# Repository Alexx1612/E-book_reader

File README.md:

## OPENBOOK E-BOOK READER
OpenBook – Proiect TSC 2025
OpenBook este un prototip de eBook reader open-source, dezvoltat în jurul microcontrolerului ESP32-C6. Dispozitivul este echipat cu un afișaj E-Ink, baterie Li-Po, încărcare prin USB-C, slot pentru card microSD și o serie de senzori de mediu. Proiectul a presupus realizarea completă a schemei electrice, proiectarea plăcii PCB, modelarea 3D și generarea fișierelor pentru fabricație.

## Diagrama bloc

### Caracteristici Cheie
- **Alimentare prin USB-C**  
  Permite programarea ușoară și încărcarea bateriei, asigurând o integrare simplificată cu sursa de alimentare.
- **Microcontroller ESP32-C6**  
  Dispune de un nucleu RISC-V, Wi-Fi 6, BLE și 8MB memorie flash internă pentru aplicații complexe și conectivitate modernă.
- **Senzori Integrați**  
  - **BME688:** Măsoară temperatura, umiditatea, presiunea și concentrațiile de gaze.  
  - **DS3231:** Modul RTC de înaltă precizie, care menține ceasul de timp real chiar și în absența alimentării principale.
- **Stocare Suplimentară**  
  - **Card SD (SPI):** Permite stocarea locală a e-book-urilor și datelor adiționale.  
  - **Memorie NOR Flash (W25Q512):** Oferă spațiu suplimentar de stocare prin interfața SPI.
- **Afișaj E-Paper**  
  Realizează afișajul e-book-urilor cu consum ultra-redus, prin actualizări doar la nevoie.
- **Monitorizare Baterie**  
  Modulul MAX17048 monitorizează nivelul de încărcare al bateriei, contribuind la gestionarea eficientă a consumului de energie.

## Bill of materials (BOM)

| Component                          | Supplier Link                                                                                                                                                 | Datasheet                                                                                                         |
|------------------------------------|---------------------------------------------------------------------------------------------------------------------------------------------------------------|-------------------------------------------------------------------------------------------------------------------|
| XC6220A331MR-G                     | [Model](https://componentsearchengine.com/part-view/XC6220A331MR-G/Torex)                                                                                      | [Datasheet](https://product.torexsemi.com/system/files/series/xc6220.pdf)                                            |
| W25Q512JVEIQ                       | [Model](https://www.snapeda.com/parts/W25Q512JVEIQ/Winbond+Electronics/view-part/?ref=eda)                                                                        | [Datasheet](https://www.winbond.com/resource-files/W25Q512JV%20SPI%20RevB%2006252019%20KMS.pdf)                      |
| USBLC6-2SC6Y                       | [Model](https://www.snapeda.com/parts/USBLC6-2SC6Y/STMicroelectronics/view-part/?welcome=home&ref=eda)                                                            | [Datasheet](https://www.snapeda.com/parts/USBLC6-2SC6Y/STMicroelectronics/datasheet/)                              |
| USB4110-GF-A                       | [Model](https://componentsearchengine.com/part-view/USB4110-GF-A/GCT%20(GLOBAL%20CONNECTOR%20TECHNOLOGY))                                                        | [Datasheet](https://gct.co/files/drawings/usb4110.pdf)                                                             |
| SJ                                 | [Model](https://grabcad.com/library/solder-jumpers-1)                                                                                                          | [Datasheet]()                                                                                                     |
| SI1308EDL-T1-GE3 MOSFET             | [Model](https://www.snapeda.com/parts/SI1308EDL-T1-GE3/Vishay+Siliconix/view-part/?welcome=home&ref=eda)                                                        | [Datasheet](https://www.snapeda.com/parts/SI1308EDL-T1-GE3/Vishay%20Siliconix/datasheet/)                           |
| Resistor 0402                      | [Model](https://grabcad.com/library/resistor-0402-1)                                                                                                           | [Datasheet](https://www.yageo.com/upload/media/product/products/datasheet/rchip/PYu-RC_Group_51_RoHS_L_12.pdf)       |
| RCL CPOL 3528                      | [Model](https://www.snapeda.com/parts/CPH3225A/Seiko+Instruments/view-part/?ref=eda)                                                                             | [Datasheet](https://s3.amazonaws.com/snapeda/datasheet/TAJB475K025RNJ_AVX.pdf)                                     |
| QWIIC Connector                    | [Model](https://www.snapeda.com/parts/PRT-14417/SparkFun/view-part/)                                                                                           | [Datasheet](https://www.snapeda.com/parts/PRT-14417/SparkFun%20Electronics/datasheet/)                              |
| PGB1010603MR                       | [Model](https://www.snapeda.com/parts/PGB1010603MR/Littelfuse/view-part/?ref=eda)                                                                               | [Datasheet](https://www.snapeda.com/parts/PGB1010603MR/Littelfuse%20Inc./datasheet/)                                |
| MBR0530 Schottky Diode             | [Model](https://www.snapeda.com/parts/MBR0530/Onsemi/view-part/?ref=snap)                                                                                        | [Datasheet](https://www.snapeda.com/parts/MBR0530/ON%20Semiconductor/datasheet/)                                   |
| MAX17048G+T10                      | [Model](https://www.snapeda.com/parts/MAX17048G+T10/Analog+Devices/view-part/?ref=eda)                                                                            | [Datasheet](https://www.snapeda.com/parts/MAX17048G+T10/Analog%20Devices/datasheet/)                                |
| LED Chip 0603                      | [Model](https://www.snapeda.com/parts/KP-1608SURCK/Kingbright/view-part/?ref=search&t=LED%200603)                                                                 | [Datasheet](https://www.snapeda.com/parts/KP-1608SURCK/Kingbright/datasheet/)                                      |
| FH34SRJ-24S-0.5SH                  | [Model](https://ro.mouser.com/ProductDetail/Hirose-Connector/FH34SRJ-24S-0.5SH99?qs=vcbW%252B4%252BSTIpKBl5ap9J8Fw%3D%3D)                                       | [Datasheet](https://www.snapeda.com/parts/FH34SRJ-24S-0.5SH(99)/Hirose%20Connector/datasheet/)                     |
| ESP32C6 WROOM-1-N8                 | [Model](https://www.snapeda.com/parts/ESP32-C6-WROOM-1-N8/Espressif+Systems/view-part/?ref=eda)                                                                    | [Datasheet](https://www.snapeda.com/parts/ESP32-C6-WROOM-1-N8/Espressif%20Systems/datasheet/)                       |
| ESP32C6 Varistor 1812              | [Model]()                                                                                                                                                      | [Datasheet]()                                                                                                     |
| ESP32 WROVER MCP73831 Power Management | [Model](https://www.snapeda.com/parts/BME680/Bosch/view-part/?welcome=home)                                                                                 | [Datasheet](https://www.snapeda.com/parts/MCP73831T-2ACI/OT/Microchip/datasheet/)                                  |
| ESP32 WROVER BME680 Sensor         | [Model](https://www.snapeda.com/parts/BME680/Bosch/view-part/?welcome=home)                                                                                     | [Datasheet](https://www.bosch-sensortec.com/media/boschsensortec/downloads/datasheets/bst-bme680-ds001.pdf)         |
| ESP32 WROVER 0805 Capacitor        | [Model]()                                                                                                                                                      | [Datasheet]()                                                                                                     |
| DS3231SN                           | [Model](https://www.snapeda.com/parts/DS3231SN%23/Analog+Devices/view-part/?ref=eda)                                                                             | [Datasheet](https://www.snapeda.com/parts/DS3231SN%23/Analog%20Devices/datasheet/)                                  |
| Custom Button                      | [Model](https://industry.panasonic.com/global/en/products/control/switch/light-touch/number/evqpuj02k)                                                            | [Datasheet](https://industry.panasonic.com/global/en/downloads?tab=catalog&small_g_cd=203&part_no=EVQPUJ02K)         |
| CPH3225A                         | [Model](https://www.snapeda.com/parts/CPH3225A/Seiko+Instruments/view-part/?ref=snap)                                                                           | [Datasheet](https://www.snapeda.com/parts/CPH3225A/Seiko%20Instruments/datasheet/)                                |
| Capacitor 0402                     | [Model](https://ro.mouser.com/c/passive-components/capacitors/ceramic-capacitors/?q=CC0402&srsltid=AfmBOoogjqwwed3xvp6V5-bfVkRuawirfMcnAC47L-UQdC3mnXJk097M) | [Datasheet](https://componentsearchengine.com/Datasheets/2/CC0402MRX5R5BB106.pdf)                                  |
| BD5229G-TR                         | [Model](https://componentsearchengine.com/part-view/BD5229G-TR/ROHM%20Semiconductor)                                                                            | [Datasheet](https://fscdn.rohm.com/en/products/databook/datasheet/ic/power/voltage_detector/bd52xxg-e.pdf)         |
| 744043680                          | [Model](https://ro.mouser.com/ProductDetail/Wurth-Elektronik/744043680?qs=PGXP4M47uW6VkZq%252BkzjrHA%3D%3D)                                                   | [Datasheet](https://www.we-online.com/components/products/datasheet/744043680.pdf)                                  |
| 112A-TAAR-R03                      | [Model](https://store.comet.srl.ro/Catalogue/Product/43497/)                                                                                                  | [Datasheet](https://www.snapeda.com/parts/112A-TAAR-R03/Attend/datasheet/)                                         |

## Consum

| Component                        | Current Draw (mA) | Voltage (V) | Power (mW)   |
|----------------------------------|-------------------|-------------|--------------|
| ESP32-C6 (Wi-Fi active)          | 200               | 3.3         | 660          |
| E-Paper Display (Updating)       | 40                | 3.3         | 132          |
| BME688 Sensor (Measuring)        | 3.1               | 3.3         | 10.23        |
| RTC Module (Active)              | 0.15              | 3.3         | 0.495        |
| SD Card (Active)                 | 50                | 3.3         | 165          |
| Externar NOR Flash               | 25                | 3.3         | 82.5         |
| **Total Estimated Power Consumption** | ~318.5 mA         | 3.3         | 1050.72      |

### Arhitectura Hardware
- **Alimentare și Protecție:**  
  Sistemul beneficiază de alimentare prin USB-C și include protecții ESD (varistori, diodă TVS) pentru siguranța componentelor. Circuitul de încărcare Li-Po (MCP73831) și regulatorul LDO asigură o tensiune stabilă de 3.3V.
- **Conectivitate și Interfețe:**  
  Microcontrollerul ESP32-C6-WROOM-1 acționează ca nucleu central, conectând diferite periferice prin:
  - **SPI:** Utilizat pentru afișajul E-Paper, Cardul SD și memoria NOR Flash.  
  - **I2C:** Folosit pentru senzorii BME688 și DS3231, precum și pentru monitorizarea bateriei.  
  - **GPIO:** Gestionarea butoanelor de control (RESET, BOOT) și alte funcții digitale.

### Mapare Pini ESP32-C6
| Component                                | ESP32-C6 Pin(s)                                                     | Interface | Scop                                                                                   |
|------------------------------------------|---------------------------------------------------------------------|-----------|----------------------------------------------------------------------------------------|
| **E-Paper Display**                      | IO7 (MOSI), IO6 (SCK), IO10 (CS), IO5 (DC), IO23 (RST), IO3 (BUSY)    | SPI       | Transferă datele imaginii către afișaj și controlează starea acestuia.                  |
| **Battery Monitoring (MAX17048)**        | IO21 (SDA), IO22 (SCL)                                               | I2C       | Monitorizează tensiunea bateriei și starea de încărcare pentru un management energetic eficient. |
| **USB-C Connection**                     | GPIOs prin circuit de protecție și reglementare                       | USB       | Furnizează alimentarea și permite programarea ESP32-C6.   
| **MicroSD Card**                         | IO7 (MOSI), IO6 (SCK), IO4 (SS_SD), IO2 (MISO)                        | SPI       | Permite stocarea și accesarea fișierelor de e-book.                                     |
| **Environmental Sensor (BME688)**        | IO21 (SDA), IO22 (SCL)                                               | I2C       | Măsoară temperatura, umiditatea, presiunea și calitatea aerului.                        |
| **RTC Module (DS3231)**                  | IO21 (SDA), IO22 (SCL), IO18 (RST), IO1 (32KHz), IO0 (INT_RTC)         | I2C       | Menține ceasul de timp real în mod precis, chiar și în absența alimentării principale.    |
| **External NOR Flash**                   | IO11 (CS), IO6 (SCK), IO2 (MISO), IO7 (MOSI)                          | SPI       | Oferă stocare suplimentară pentru datele aplicațiilor și firmware.                      |
| **Control Buttons**                      | IO9 (BOOT), IO15 (CHANGE), EN (RESET)                                  | GPIO      | Permite interacțiunea utilizatorului prin funcții de boot, reset și alte comenzi digitale.|        

## Observații Suplimentare

- Traseele de alimentare au o lățime de 0.3 mm, iar traseele de semnal sunt proiectate cu o lățime de 0.15 mm, pentru a asigura o transmisie clară și o pierdere minimă de semnal.
- PCB-ul are o grosime de 1 mm și include planuri de masă pe ambele straturi, pentru a optimiza împământarea și a reduce interferențele electromagnetice.
- Conectorii, afișajul E-Paper și bateria au fost integrate în modelul 3D, iar acestea au fost testate riguros pentru a asigura o potrivire perfectă în carcasă.
- Carcasa a fost importată și aliniată cu placa pentru a obține render-uri vizuale realiste, facilitând astfel evaluarea designului final.
- Toate fișierele de proiect au fost verificate prin ERC (Electrical Rules Check) și DRC (Design Rules Check) pentru a asigura conformitatea cu standardele de proiectare și a elimina eventualele erori de fabricație.

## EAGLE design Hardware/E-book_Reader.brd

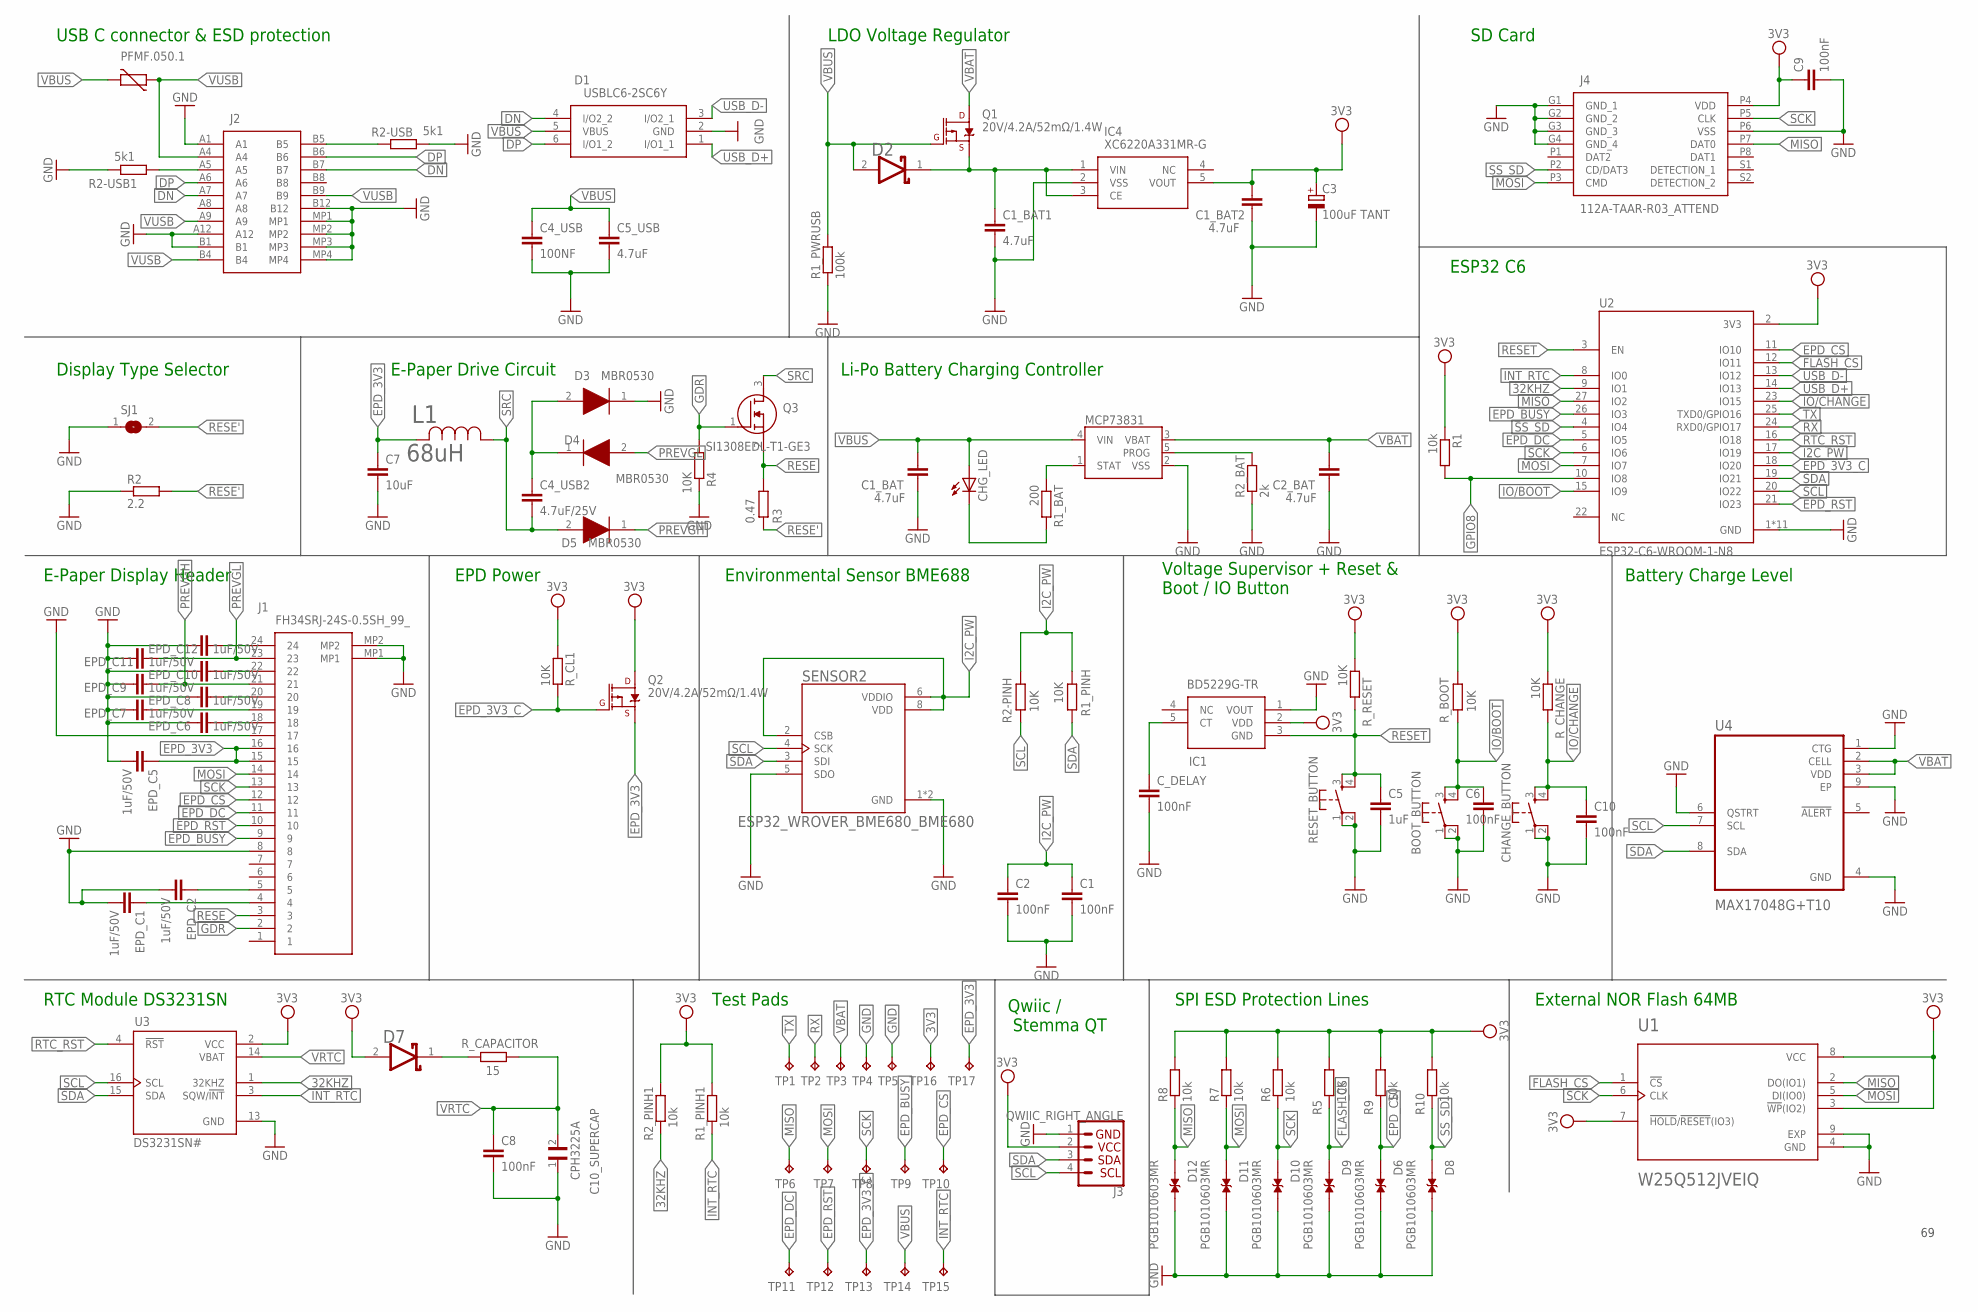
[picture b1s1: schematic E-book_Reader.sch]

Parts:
BOOT_BUTTON: BUTTON_CUSYOMV1; MYBUTTON
C1, C2, C6, C8, C9, C10: 100nF; EAGLE-LTSPICE_C0402
C1_BAT, C1_BAT1, C1_BAT2, C2_BAT, C5_USB: 4.7uF; EAGLE-LTSPICE_C0402
C3: 100uF TANT; RCL_CT3528
C4_USB: 100NF; EAGLE-LTSPICE_C0402
C4_USB2: 4.7uF/25V; EAGLE-LTSPICE_C0402
C5: 1uF; EAGLE-LTSPICE_C0402
C7: 10uF; EAGLE-LTSPICE_C0402
C10_SUPERCAP: CPH3225A; CAPCP3225X100N
CHANGE_BUTTON: BUTTON_CUSYOMV1; MYBUTTON
CHG_LED: ADAFRUIT_LEDCHIP-LED0603; ADAFRUIT_CHIP-LED0603
C_DELAY: 100nF; EAGLE-LTSPICE_C0402
D1: USBLC6-2SC6Y; SOT95P280X145-6N
D2, D7: ESP32_WROVER_AVX---SD0805S020S1R0_AVX_SD0805S020S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; ESP32_WROVER_AVX---SD0805S020S1R0_AVX_SD0805S020S1R0_0
D3, D4, D5: MBR0530; SOD3716X135N
D6, D8, D9, D10, D11, D12: PGB1010603MR; DIOC1608X36N
EPD_C1, EPD_C2, EPD_C5, EPD_C6, EPD_C7, EPD_C8, EPD_C9, EPD_C10, EPD_C11, EPD_C12: 1uF/50V; EAGLE-LTSPICE_C0402
IC1: BD5229G-TR; SOT95P280X125-5N
IC4: XC6220A331MR-G; SOT95P280X120-5N
J1: FH34SRJ-24S-0.5SH_99_; FH34SRJ24S05SH99
J2: SAMACSYS_PARTS_USB4110-GF-A; SAMACSYS_PARTS_USB4110GFA
J3: QWIIC_RIGHT_ANGLE; JST04_1MM_RA
J4: 112A-TAAR-R03_ATTEND; 112ATAARR03ATTEND
L1: 68uH; IND_4828-WE-TPC_WRE
MCP73831: ESP32_WROVER_SPARKFUN-IC-POWER_MCP73831; ESP32_WROVER_SPARKFUN-IC-POWER_SOT23-5
PFMF.050.1: ESP32C6_VARISTORCN1812; ESP32C6_VARISTOR_CT/CN1812
Q1, Q2: 20V/4.2A/52mΩ/1.4W; ESP32_WROVER_SPARKFUN-DISCRETESEMI_SOT23-3
Q3: SI1308EDL-T1-GE3; SOT65P210X110-3N
R1, R1_PINH1, R2_PINH1, R5, R6, R7, R8, R9, R10: 10k; ESP32_WROVER_EAGLE-LTSPICE_R0402
R1_BAT: 200; ESP32_WROVER_EAGLE-LTSPICE_R0402
R1_PINH, R2-PINH, R4: 10K; ESP32_WROVER_EAGLE-LTSPICE_R0402
R1_PWRUSB: 100k; ESP32_WROVER_EAGLE-LTSPICE_R0402
R2: 2.2; ESP32_WROVER_EAGLE-LTSPICE_R0402
R2-USB, R2-USB1: 5k1; ESP32_WROVER_EAGLE-LTSPICE_R0402
R2_BAT: 2k; ESP32_WROVER_EAGLE-LTSPICE_R0402
R3: 0.47; ESP32_WROVER_EAGLE-LTSPICE_R0402
RESET_BUTTON: BUTTON_CUSYOMV1; MYBUTTON
R_BOOT: 10K; ESP32_WROVER_EAGLE-LTSPICE_R0402
R_CAPACITOR: 15; ESP32_WROVER_EAGLE-LTSPICE_R0402
R_CHANGE: 10K; ESP32_WROVER_EAGLE-LTSPICE_R0402
R_CL1: 10K; ESP32_WROVER_EAGLE-LTSPICE_R0402
R_RESET: 10K; ESP32_WROVER_EAGLE-LTSPICE_R0402
SENSOR2: ESP32_WROVER_BME680_BME680; ESP32_WROVER_BME680_PSON80P300X300X100-8N
SJ1: SJ
TP1, TP2, TP3, TP4, TP5, TP6, TP7, TP8, TP9, TP10, TP11, TP12, TP13, TP14, TP15, TP16, TP17: TPTP20R; TP20R
U1: W25Q512JVEIQ; SON127P600X800X80-9N
U2: ESP32-C6-WROOM-1-N8; XCVR_ESP32-C6-WROOM-1-N8
U3: DS3231SN#; SOIC127P1032X265-16N
U4: MAX17048G+T10; SON50P200X200X80-9N

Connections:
3V3: C1_BAT2.1, C3.+, C9.1, D7.2 (ANODE), IC1.2 (VDD), IC4.5 (VOUT), J3.2, J4.P4 (VDD), Q2.3 (D), R1.1, R1_PINH1.2, R2_PINH1.2, R5.2, R6.2, R7.2, R8.2, R9.2, R10.2, R_BOOT.1, R_CHANGE.1, R_CL1.1, R_RESET.1, TP16.TP, U1.3 (!WP!(IO2)), U1.7 (!HOLD!/!RESET!(IO3)), U1.8 (VCC), U2.2 (3V3), U3.2 (VCC)
32KHZ: R2_PINH1.1, U2.9 (IO1), U3.1 (32KHZ)
DN: D1.4 (I/O2_2), J2.A7, J2.B7
DP: D1.6 (I/O1_2), J2.A6, J2.B6
EPD_3V3: C7.1, EPD_C5.1, J1.15, J1.16, L1.2, Q2.2 (S), TP17.TP
EPD_3V3_C: Q2.1 (G), R_CL1.2, TP13.TP, U2.18 (IO20)
EPD_BUSY: J1.9, TP9.TP, U2.26 (IO3)
EPD_CS: D6.1, J1.12, R9.1, TP10.TP, U2.11 (IO10)
EPD_DC: J1.11, TP11.TP, U2.5 (IO5)
EPD_RST: J1.10, TP12.TP, U2.21 (IO23)
FLASH_CS: D9.1, R5.1, U1.1 (!CS), U2.12 (IO11)
GDR: J1.2, Q3.1 (G), R4.1
GND: BOOT_BUTTON.1, BOOT_BUTTON.2, C1.2, C1_BAT.2, C1_BAT1.2, C1_BAT2.2, C2.2, C2_BAT.2, C3.-, C4_USB.2, C5.2, C5_USB.2, C6.2, C7.2, C8.2, C9.2, C10.2, C10_SUPERCAP.1, CHANGE_BUTTON.1, CHANGE_BUTTON.2, C_DELAY.2, D1.2 (GND), D3.1 (K), D6.2, D8.2, D9.2, D10.2, D11.2, D12.2, EPD_C1.2, EPD_C2.2, EPD_C5.2, EPD_C6.2, EPD_C7.2, EPD_C8.2, EPD_C9.2, EPD_C10.2, EPD_C11.2, EPD_C12.2, IC1.1 (VOUT), IC4.2 (VSS), J1.8, J1.17, J1.MP1, J1.MP2, J2.A1, J2.A12, J2.B1, J2.B12, J2.MP1, J2.MP2, J2.MP3, J2.MP4, J3.1, J4.G1 (GND_1), J4.G2 (GND_2), J4.G3 (GND_3), J4.G4 (GND_4), J4.P6 (VSS), MCP73831.2 (VSS), R1_PWRUSB.1, R2.1, R2-USB.2, R2-USB1.1, R2_BAT.1, R4.2, RESET_BUTTON.1, RESET_BUTTON.2, SENSOR2.1 (GND), SENSOR2.5 (SDO), SENSOR2.7 (GND), SJ1.1, TP4.TP, TP5.TP, U1.4 (GND), U1.9 (EXP), U2.1 (GND), U2.28 (GND), U2.29_1 (GND), U2.29_2 (GND), U2.29_3 (GND), U2.29_4 (GND), U2.29_5 (GND), U2.29_6 (GND), U2.29_7 (GND), U2.29_8 (GND), U2.29_9 (GND), U3.13 (GND), U4.1 (CTG), U4.4 (GND), U4.6 (QSTRT), U4.9 (EP)
GPIO8: R1.2, U2.10 (IO8)
I2C_PW: C1.1, C2.1, R1_PINH.2, R2-PINH.2, SENSOR2.2 (CSB), SENSOR2.6 (VDDIO), SENSOR2.8 (VDD), U2.17 (IO19)
INT_RTC: R1_PINH1.1, TP15.TP, U2.8 (IO0), U3.3 (SQW/!INT)
IO/BOOT: BOOT_BUTTON.3, BOOT_BUTTON.4, C6.1, R_BOOT.2, U2.15 (IO9)
IO/CHANGE: C10.1, CHANGE_BUTTON.3, CHANGE_BUTTON.4, R_CHANGE.2, U2.23 (IO15)
MISO: D12.1, J4.P7 (DAT0), R8.1, TP6.TP, U1.2 (DO(IO1)), U2.27 (IO2)
MOSI: D11.1, J1.14, J4.P3 (CMD), R7.1, TP7.TP, U1.5 (DI(IO0)), U2.7 (IO7)
unnamed: J2.B5, R2-USB.1
unnamed: MCP73831.1 (STAT), R1_BAT.1
unnamed: J2.A5, R2-USB1.2
unnamed: EPD_C12.1, J1.24
unnamed: EPD_C8.1, J1.20
unnamed: EPD_C10.1, J1.22
unnamed: EPD_C7.1, J1.19
unnamed: C1_BAT1.1, D2.1 (CATHODE), IC4.1 (VIN), IC4.3 (CE), Q1.2 (S)
unnamed: EPD_C6.1, J1.18
unnamed: C4_USB2.1, D3.2 (A), D4.1 (K)
unnamed: CHG_LED.C, R1_BAT.2
unnamed: MCP73831.5 (PROG), R2_BAT.2
unnamed: EPD_C1.1, J1.4
unnamed: EPD_C2.1, J1.5
unnamed: C_DELAY.1, IC1.5 (CT)
unnamed: D7.1 (CATHODE), R_CAPACITOR.2
PREVGH: D5.1 (K), EPD_C9.1, J1.21
PREVGL: D4.2 (A), EPD_C11.1, J1.23
RESE: J1.3, Q3.2 (S), R3.2
RESE': R2.2, R3.1, SJ1.2
RESET: C5.1, IC1.3 (GND), RESET_BUTTON.3, RESET_BUTTON.4, R_RESET.2, U2.3 (EN)
RTC_RST: U2.16 (IO18), U3.4 (!RST)
RX: TP2.TP, U2.24 (RXD0/GPIO17)
SCK: D10.1, J1.13, J4.P5 (CLK), R6.1, TP8.TP, U1.6 (CLK), U2.6 (IO6)
SCL: J3.4, R2-PINH.1, SENSOR2.4 (SCK), U2.20 (IO22), U3.16 (SCL), U4.7 (SCL)
SDA: J3.3, R1_PINH.1, SENSOR2.3 (SDI), U2.19 (IO21), U3.15 (SDA), U4.8 (SDA)
SRC: C4_USB2.2, D5.2 (A), L1.1, Q3.3 (D)
SS_SD: D8.1, J4.P2 (CD/DAT3), R10.1, U2.4 (IO4)
TX: TP1.TP, U2.25 (TXD0/GPIO16)
USB_D+: D1.1 (I/O1_1), U2.14 (IO13)
USB_D-: D1.3 (I/O2_1), U2.13 (IO12)
VBAT: C2_BAT.1, MCP73831.3 (VBAT), Q1.3 (D), TP3.TP, U4.2 (CELL), U4.3 (VDD)
VBUS: C1_BAT.1, C4_USB.1, C5_USB.1, CHG_LED.A, D1.5 (VBUS), D2.2 (ANODE), MCP73831.4 (VIN), PFMF.050.1.2, Q1.1 (G), R1_PWRUSB.2, TP14.TP
VRTC: C8.1, C10_SUPERCAP.2, R_CAPACITOR.1, U3.14 (VBAT)
VUSB: J2.A4, J2.A9, J2.B4, J2.B9, PFMF.050.1.1

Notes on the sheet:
USB C connector & ESD protection
LDO Voltage Regulator
SD Card
ESP32 C6
Display Type Selector
E-Paper Drive Circuit
Li-Po Battery Charging Controller
E-Paper Display Header
EPD Power
Environmental Sensor BME688
Voltage Supervisor + Reset & Boot / IO Button
Battery Charge Level
External NOR Flash 64MB
SPI ESD Protection Lines
Qwiic / Stemma QT
Test Pads
RTC Module DS3231SN

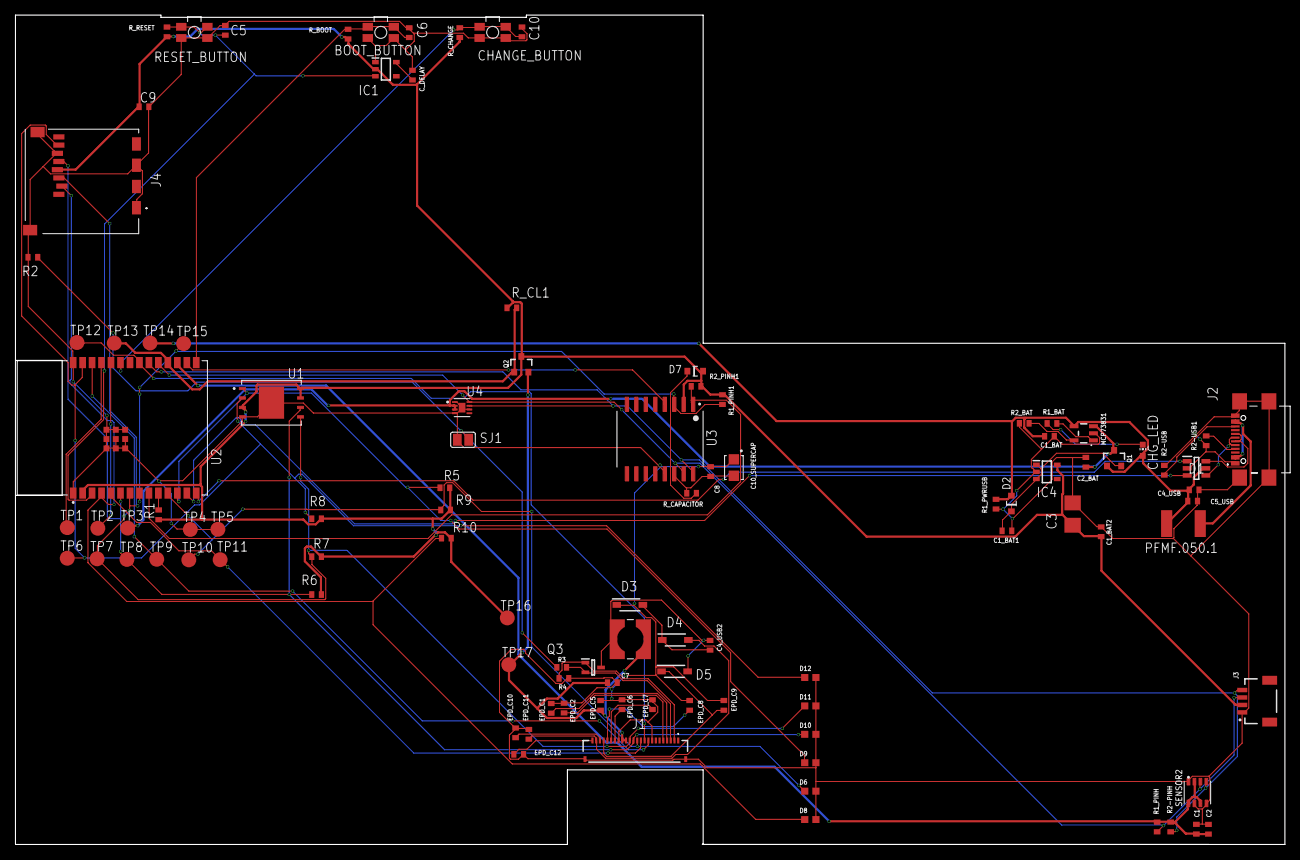
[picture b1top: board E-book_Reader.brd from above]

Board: 2 copper layers, 170.2 x 111.2 mm, 103 parts (0 on the bottom side), 55 nets.

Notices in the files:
parts and their libraries:
COPYRIGHT: Copyright (C) 2024 Ultra Librarian. All rights reserved.
